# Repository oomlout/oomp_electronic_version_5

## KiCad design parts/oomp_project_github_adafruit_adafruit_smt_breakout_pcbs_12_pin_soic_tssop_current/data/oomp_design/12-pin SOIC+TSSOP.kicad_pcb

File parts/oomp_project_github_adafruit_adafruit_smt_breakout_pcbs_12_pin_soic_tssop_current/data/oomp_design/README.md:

# OOMP KiCad design copy

Open `12-pin SOIC+TSSOP.kicad_pro` (or the `.kicad_pcb` / `.kicad_sch`) in KiCad. Local OOMP libraries are under `libraries/`. Original inputs are preserved in [../original/](../original/).

Only verified unchanged installed KiCad defaults were renamed. Modified, custom, unmatched and unavailable items remain unchanged. Soldering variants are never swapped during conversion. Existing pad coordinates, nets and UUIDs are preserved.

See [conversion_report.yaml](conversion_report.yaml) for every conversion and skip. Copy this directory before editing; regeneration refuses to overwrite edited design files.

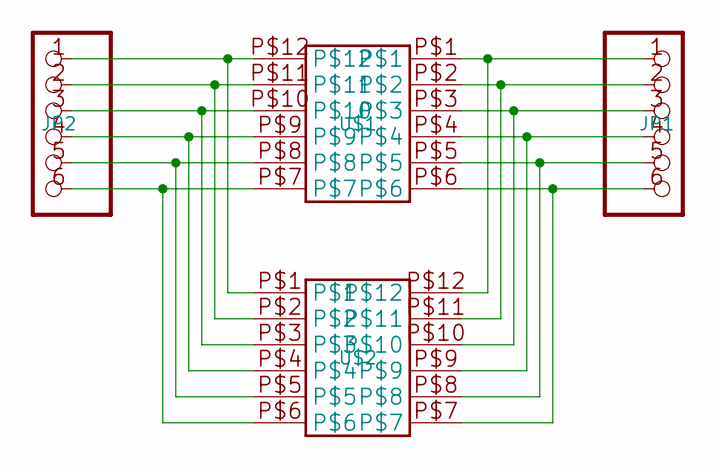
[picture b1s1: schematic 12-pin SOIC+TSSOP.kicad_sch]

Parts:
JP1, JP2: PADS-6
U$1: 12-PINTSSOP-NW; TSSOP12-NW
U$2: 12-PINSOIC-NW; SO12-NW

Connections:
unnamed: JP2.2, U$1.P$11, U$2.P$2
unnamed: JP2.3, U$1.P$10, U$2.P$3
unnamed: JP2.4, U$1.P$9, U$2.P$4
unnamed: JP2.5, U$1.P$8, U$2.P$5
unnamed: JP2.6, U$1.P$7, U$2.P$6
unnamed: JP1.1, U$1.P$1, U$2.P$12
unnamed: JP1.2, U$1.P$2, U$2.P$11
unnamed: JP1.3, U$1.P$3, U$2.P$10
unnamed: JP1.4, U$1.P$4, U$2.P$9
unnamed: JP1.5, U$1.P$5, U$2.P$8
unnamed: JP1.6, U$1.P$6, U$2.P$7
unnamed: JP2.1, U$1.P$12, U$2.P$1

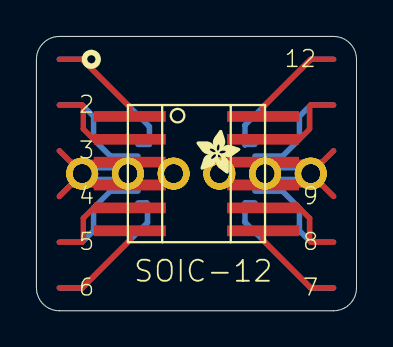
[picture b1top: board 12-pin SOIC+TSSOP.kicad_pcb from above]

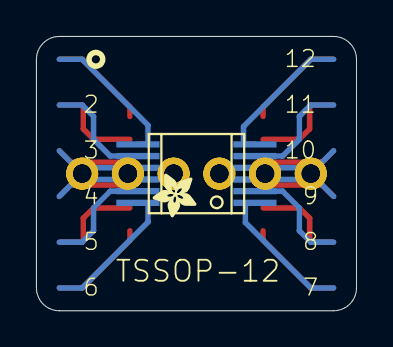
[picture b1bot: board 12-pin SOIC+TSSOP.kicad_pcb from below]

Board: 2 copper layers, 17.8 x 15.2 mm, 6 parts (2 on the bottom side), 12 nets.

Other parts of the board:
U$3, U$4: ADAFRUIT_2.5MM

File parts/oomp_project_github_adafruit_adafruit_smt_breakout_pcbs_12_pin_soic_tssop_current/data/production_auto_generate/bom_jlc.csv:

Comment,Designator,Footprint,LCSC Part #
,"U$3,U$4",12-pin SOIC+TSSOP-import-fps:ADAFRUIT_2.5MM,
,"JP1,JP2",12-pin SOIC+TSSOP-import-fps:PADS-6,
12-PINSOIC-NW,U$2,12-pin SOIC+TSSOP-import-fps:SO12-NW,
12-PINTSSOP-NW,U$1,12-pin SOIC+TSSOP-import-fps:TSSOP12-NW,

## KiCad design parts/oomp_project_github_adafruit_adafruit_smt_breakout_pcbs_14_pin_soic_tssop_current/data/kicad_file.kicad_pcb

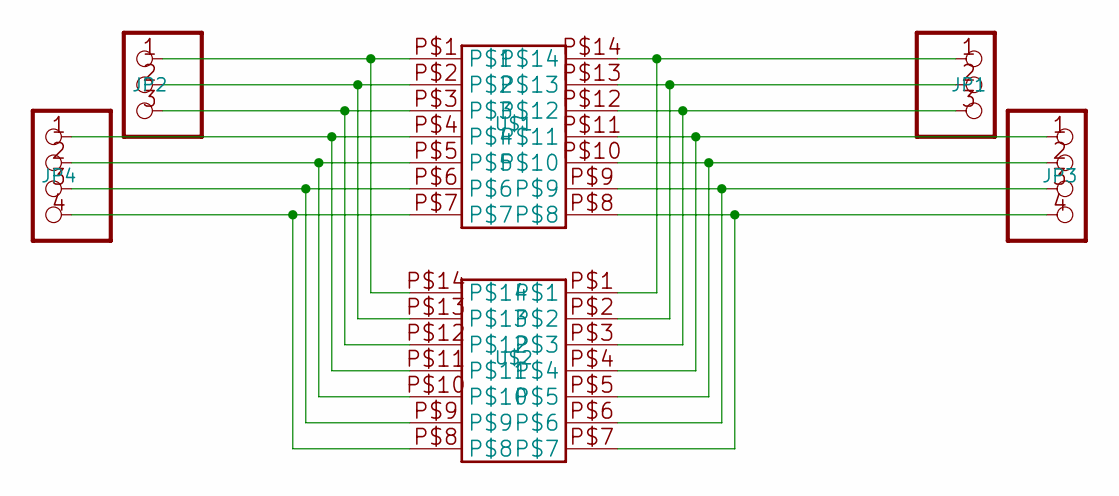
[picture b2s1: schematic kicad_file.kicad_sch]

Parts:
JP1, JP2: PADS-3
JP3, JP4: PADS-4
U$1: 14-PINSOIC-NW; SO14-NW
U$2: 14-PINTSSOP-NW; TSSOP14-NW

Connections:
unnamed: JP2.1, U$1.P$1, U$2.P$14
unnamed: JP2.2, U$1.P$2, U$2.P$13
unnamed: JP2.3, U$1.P$3, U$2.P$12
unnamed: JP4.1, U$1.P$4, U$2.P$11
unnamed: JP4.2, U$1.P$5, U$2.P$10
unnamed: JP4.3, U$1.P$6, U$2.P$9
unnamed: JP4.4, U$1.P$7, U$2.P$8
unnamed: JP1.1, U$1.P$14, U$2.P$1
unnamed: JP1.2, U$1.P$13, U$2.P$2
unnamed: JP1.3, U$1.P$12, U$2.P$3
unnamed: JP3.1, U$1.P$11, U$2.P$4
unnamed: JP3.2, U$1.P$10, U$2.P$5
unnamed: JP3.3, U$1.P$9, U$2.P$6
unnamed: JP3.4, U$1.P$8, U$2.P$7

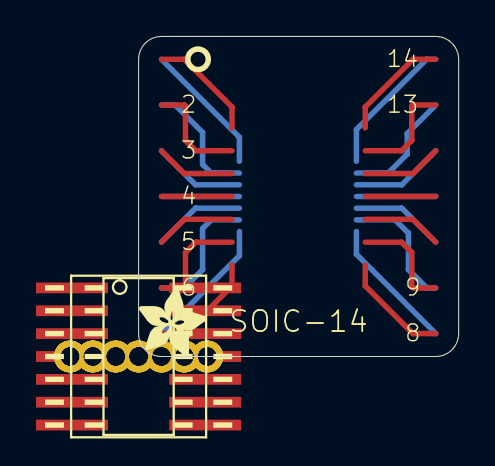
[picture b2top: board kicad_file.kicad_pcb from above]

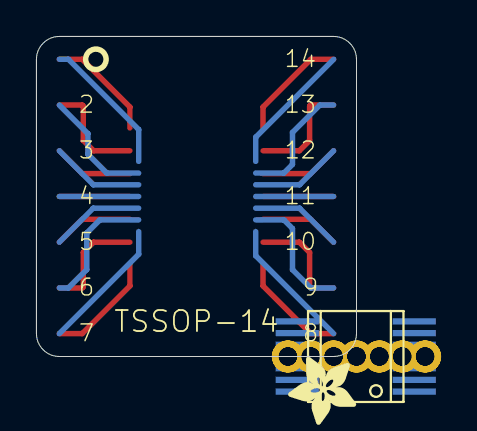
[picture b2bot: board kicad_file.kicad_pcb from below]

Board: 2 copper layers, 17.8 x 17.8 mm, 8 parts (2 on the bottom side), 14 nets.

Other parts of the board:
U$3, U$4: ADAFRUIT_3.5MM

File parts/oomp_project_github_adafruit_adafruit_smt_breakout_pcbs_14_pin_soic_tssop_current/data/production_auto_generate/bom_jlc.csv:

Comment,Designator,Footprint,LCSC Part #
,"U$3,U$4",14-pin SOIC+TSSOP-import-fps:ADAFRUIT_3.5MM,
,"JP1,JP2",14-pin SOIC+TSSOP-import-fps:PADS-3,
,"JP3,JP4",14-pin SOIC+TSSOP-import-fps:PADS-4,
14-PINSOIC-NW,U$1,14-pin SOIC+TSSOP-import-fps:SO14-NW,
14-PINTSSOP-NW,U$2,14-pin SOIC+TSSOP-import-fps:TSSOP14-NW,

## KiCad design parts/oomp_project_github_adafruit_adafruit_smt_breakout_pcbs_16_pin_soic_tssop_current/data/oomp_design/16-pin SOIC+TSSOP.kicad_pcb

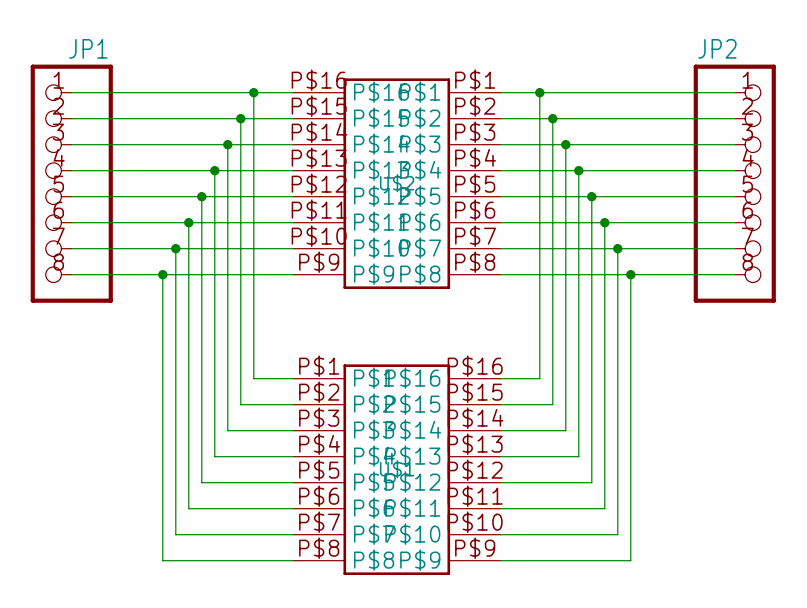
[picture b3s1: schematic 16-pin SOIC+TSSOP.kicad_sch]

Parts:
JP1, JP2: PADS-8CLEANBIG; PADS-8
U$1: 16-PINSOIC-NW; SO16-NW
U$2: 16-PINTSSOP-NW; TSSOP16-NW

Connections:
unnamed: JP1.1, U$1.P$1, U$2.P$16
unnamed: JP1.2, U$1.P$2, U$2.P$15
unnamed: JP1.3, U$1.P$3, U$2.P$14
unnamed: JP1.4, U$1.P$4, U$2.P$13
unnamed: JP1.6, U$1.P$6, U$2.P$11
unnamed: JP1.7, U$1.P$7, U$2.P$10
unnamed: JP1.8, U$1.P$8, U$2.P$9
unnamed: JP2.1, U$1.P$16, U$2.P$1
unnamed: JP2.2, U$1.P$15, U$2.P$2
unnamed: JP2.3, U$1.P$14, U$2.P$3
unnamed: JP2.4, U$1.P$13, U$2.P$4
unnamed: JP2.5, U$1.P$12, U$2.P$5
unnamed: JP2.6, U$1.P$11, U$2.P$6
unnamed: JP2.7, U$1.P$10, U$2.P$7
unnamed: JP2.8, U$1.P$9, U$2.P$8
unnamed: JP1.5, U$1.P$5, U$2.P$12

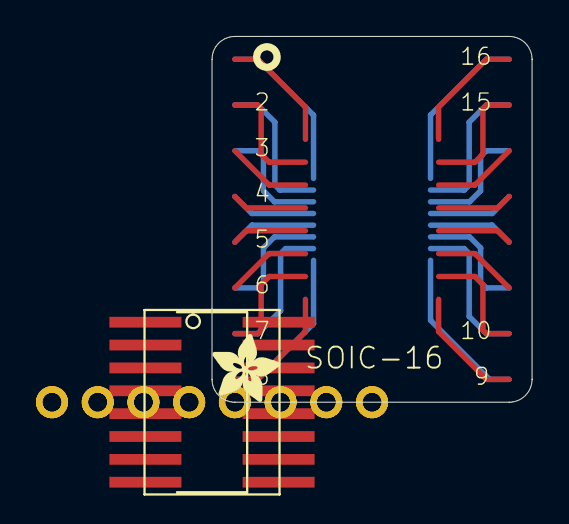
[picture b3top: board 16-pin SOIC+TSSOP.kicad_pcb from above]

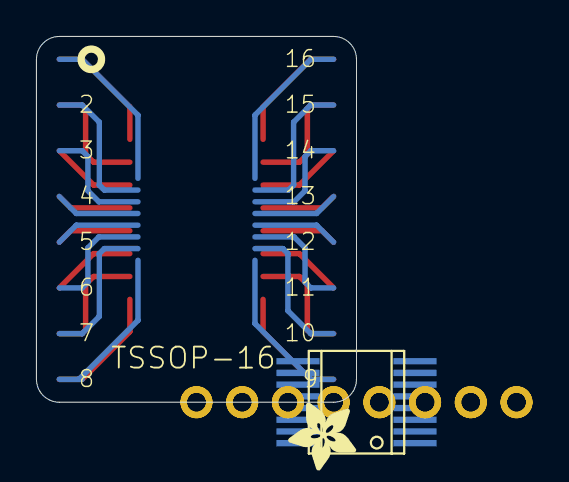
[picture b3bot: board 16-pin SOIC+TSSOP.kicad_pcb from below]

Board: 2 copper layers, 17.8 x 20.3 mm, 6 parts (2 on the bottom side), 16 nets.

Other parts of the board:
U$3, U$4: ADAFRUIT_3.5MM

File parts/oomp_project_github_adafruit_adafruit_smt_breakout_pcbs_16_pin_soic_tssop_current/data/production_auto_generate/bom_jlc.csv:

Comment,Designator,Footprint,LCSC Part #
,"U$3,U$4",16-pin SOIC+TSSOP-import-fps:ADAFRUIT_3.5MM,
,"JP1,JP2",16-pin SOIC+TSSOP-import-fps:PADS-8,
16-PINSOIC-NW,U$1,16-pin SOIC+TSSOP-import-fps:SO16-NW,
16-PINTSSOP-NW,U$2,16-pin SOIC+TSSOP-import-fps:TSSOP16-NW,

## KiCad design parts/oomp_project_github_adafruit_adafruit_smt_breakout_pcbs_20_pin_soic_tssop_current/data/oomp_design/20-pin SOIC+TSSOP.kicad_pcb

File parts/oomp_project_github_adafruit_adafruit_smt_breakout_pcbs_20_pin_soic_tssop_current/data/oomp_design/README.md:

# OOMP KiCad design copy

Open `20-pin SOIC+TSSOP.kicad_pro` (or the `.kicad_pcb` / `.kicad_sch`) in KiCad. Local OOMP libraries are under `libraries/`. Original inputs are preserved in [../original/](../original/).

Only verified unchanged installed KiCad defaults were renamed. Modified, custom, unmatched and unavailable items remain unchanged. Soldering variants are never swapped during conversion. Existing pad coordinates, nets and UUIDs are preserved.

See [conversion_report.yaml](conversion_report.yaml) for every conversion and skip. Copy this directory before editing; regeneration refuses to overwrite edited design files.

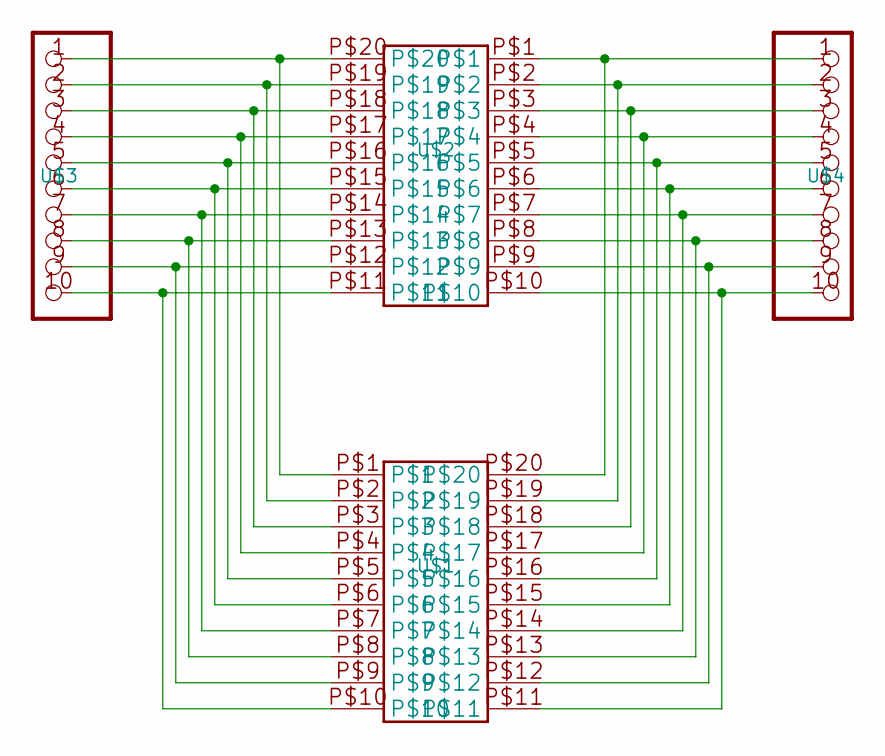
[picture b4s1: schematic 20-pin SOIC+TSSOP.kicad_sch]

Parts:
U$1: 20-PINSOIC-NW; SO20-NW
U$2: 20-PINTSSOP-NW; TSSOP20-NW
U$3, U$4: PADS-10

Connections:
unnamed: U$1.P$1, U$2.P$20, U$3.1
unnamed: U$1.P$2, U$2.P$19, U$3.2
unnamed: U$1.P$3, U$2.P$18, U$3.3
unnamed: U$1.P$4, U$2.P$17, U$3.4
unnamed: U$1.P$5, U$2.P$16, U$3.5
unnamed: U$1.P$6, U$2.P$15, U$3.6
unnamed: U$1.P$7, U$2.P$14, U$3.7
unnamed: U$1.P$8, U$2.P$13, U$3.8
unnamed: U$1.P$9, U$2.P$12, U$3.9
unnamed: U$1.P$10, U$2.P$11, U$3.10
unnamed: U$1.P$20, U$2.P$1, U$4.1
unnamed: U$1.P$19, U$2.P$2, U$4.2
unnamed: U$1.P$18, U$2.P$3, U$4.3
unnamed: U$1.P$17, U$2.P$4, U$4.4
unnamed: U$1.P$16, U$2.P$5, U$4.5
unnamed: U$1.P$15, U$2.P$6, U$4.6
unnamed: U$1.P$14, U$2.P$7, U$4.7
unnamed: U$1.P$13, U$2.P$8, U$4.8
unnamed: U$1.P$12, U$2.P$9, U$4.9
unnamed: U$1.P$11, U$2.P$10, U$4.10

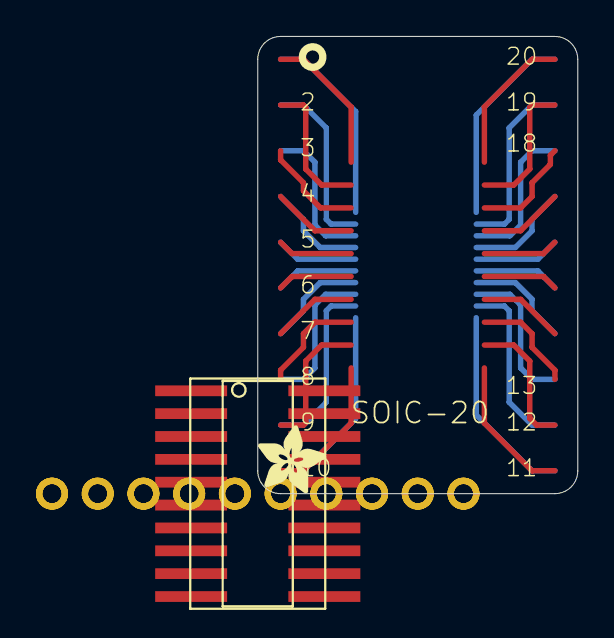
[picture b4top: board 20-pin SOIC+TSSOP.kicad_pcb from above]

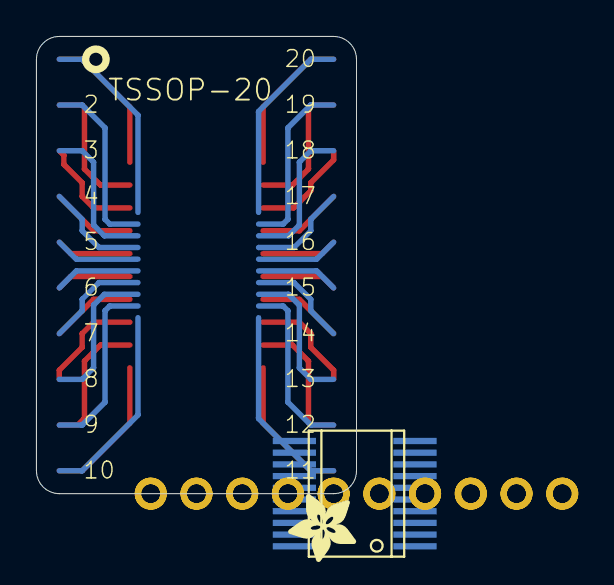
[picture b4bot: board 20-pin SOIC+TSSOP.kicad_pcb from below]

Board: 2 copper layers, 17.8 x 25.4 mm, 6 parts (2 on the bottom side), 20 nets.

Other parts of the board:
U$5, U$6: ADAFRUIT_3.5MM

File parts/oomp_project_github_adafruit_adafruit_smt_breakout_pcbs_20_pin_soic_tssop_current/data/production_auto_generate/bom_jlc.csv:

Comment,Designator,Footprint,LCSC Part #
,"U$5,U$6",20-pin SOIC+TSSOP-import-fps:ADAFRUIT_3.5MM,
,"U$3,U$4",20-pin SOIC+TSSOP-import-fps:PADS-10,
20-PINSOIC-NW,U$1,20-pin SOIC+TSSOP-import-fps:SO20-NW,
20-PINTSSOP-NW,U$2,20-pin SOIC+TSSOP-import-fps:TSSOP20-NW,
